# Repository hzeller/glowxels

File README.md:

Glowxels - Glow in the Dark Pixels
==================================

Driving 405nm LED line to make a pixelated glow-in-the-dark display.

This repo contains the addressed LED row, the rest is found in
https://github.com/hzeller/glowtape

The pitch is relatively small with 0.8mm for a width of 51.2mm with 64 LEDs.
It is achived with two rows of 1.6mm pitch with 0603 LED mounted in a
zig-zag pattern to have the adjacent pixels without visible gap in X-direction.

The row distance in Y-direction is 4 pixels apart (3.2mm), so even and odd
pixels in a row are sent 4 pixels spaced when sending.

The LEDs are driven by an [STP16CPC26]-chip - a neat 16 bit shift register with
constant current drivers. The serial data is just sent using the SPI bus
(with CS connected Latch), this is super-simple to wire.

The board carries 64 LEDs with two staggered rows of 0603 LEDs with a resulting
pixel-density of 0.8mm.

[STP16CPC26]: http://www.st.com/resource/en/datasheet/stp16cpc26.pdf

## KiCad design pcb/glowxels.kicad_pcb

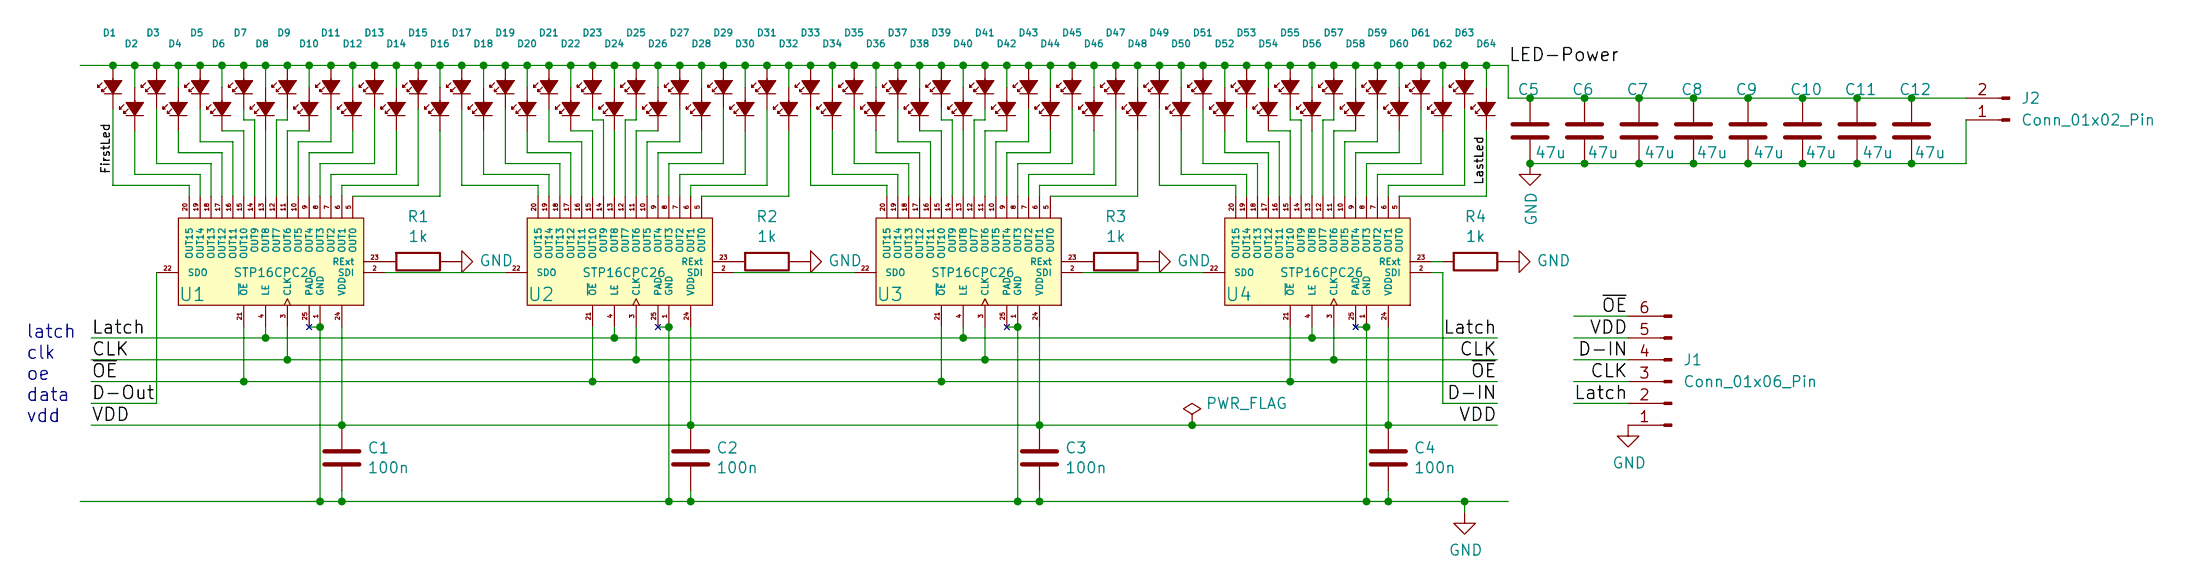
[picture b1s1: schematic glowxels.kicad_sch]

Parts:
C1, C2, C3, C4: 100n; C_0603_1608Metric
C5, C6, C7, C8, C9, C10, C11, C12: 47u; C_1210_3225Metric
D1, D2, D3, D4, D5, D6, D7, D8, D9, D10, D11, D12, D13, D14, D15, D16, D17, D18, D19, D20, D21, D22, D23, D24, D25, D26, D27, D28, D29, D30, D31, D32, D33, D34, D35, D36, D37, D38, D39, D40, D41, D42, D43, D44, D45, D46, D47, D48, D49, D50, D51, D52, D53, D54, D55, D56, D57, D58, D59, D60, D61, D62, D63, D64: UV; LED_0603_1608Metric
J1: Conn_01x06_Pin; PinHeader_1x06_P2.00mm_Vertical
J2: Conn_01x02_Pin; PinHeader_1x02_P2.00mm_Vertical
R1, R2, R3, R4: 1k; R_0603_1608Metric
U1, U2, U3, U4: STP16CPC26; TSSOP-24EP_4.4x7.8mm_Pitch0.65mm

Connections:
/CLK: J1.3, U1.3 (CLK), U2.3 (CLK), U3.3 (CLK), U4.3 (CLK)
/D-IN: J1.4, U4.2 (SDI)
/D-Out: U1.22 (SDO)
/FirstLed: D1.1 (K), U1.20 (OUT15)
/LED-Power: C5.1, C6.1, C7.1, C8.1, C9.1, C10.1, C11.1, C12.1, D1.2 (A), D2.2 (A), D3.2 (A), D4.2 (A), D5.2 (A), D6.2 (A), D7.2 (A), D8.2 (A), D9.2 (A), D10.2 (A), D11.2 (A), D12.2 (A), D13.2 (A), D14.2 (A), D15.2 (A), D16.2 (A), D17.2 (A), D18.2 (A), D19.2 (A), D20.2 (A), D21.2 (A), D22.2 (A), D23.2 (A), D24.2 (A), D25.2 (A), D26.2 (A), D27.2 (A), D28.2 (A), D29.2 (A), D30.2 (A), D31.2 (A), D32.2 (A), D33.2 (A), D34.2 (A), D35.2 (A), D36.2 (A), D37.2 (A), D38.2 (A), D39.2 (A), D40.2 (A), D41.2 (A), D42.2 (A), D43.2 (A), D44.2 (A), D45.2 (A), D46.2 (A), D47.2 (A), D48.2 (A), D49.2 (A), D50.2 (A), D51.2 (A), D52.2 (A), D53.2 (A), D54.2 (A), D55.2 (A), D56.2 (A), D57.2 (A), D58.2 (A), D59.2 (A), D60.2 (A), D61.2 (A), D62.2 (A), D63.2 (A), D64.2 (A), J2.2
/LastLed: D64.1 (K), U4.5 (OUT0)
/Latch: J1.2, U1.4 (LE), U2.4 (LE), U3.4 (LE), U4.4 (LE)
/VDD: C1.1, C2.1, C3.1, C4.1, J1.5, U1.24 (VDD), U2.24 (VDD), U3.24 (VDD), U4.24 (VDD)
/~OE: J1.6, U1.21 (~OE), U2.21 (~OE), U3.21 (~OE), U4.21 (~OE)
GND: C1.2, C2.2, C3.2, C4.2, C5.2, C6.2, C7.2, C8.2, C9.2, C10.2, C11.2, C12.2, J1.1, J2.1, R1.1, R2.1, R3.1, R4.1, U1.1 (GND), U1.25 (PAD), U2.1 (GND), U2.25 (PAD), U3.1 (GND), U3.25 (PAD), U4.1 (GND), U4.25 (PAD)
unnamed: D2.1 (K), U1.19 (OUT14)
unnamed: D3.1 (K), U1.18 (OUT13)
unnamed: D4.1 (K), U1.17 (OUT12)
unnamed: D5.1 (K), U1.16 (OUT11)
unnamed: D6.1 (K), U1.15 (OUT10)
unnamed: D7.1 (K), U1.14 (OUT9)
unnamed: D8.1 (K), U1.13 (OUT8)
unnamed: D9.1 (K), U1.12 (OUT7)
unnamed: D10.1 (K), U1.11 (OUT6)
unnamed: D11.1 (K), U1.10 (OUT5)
unnamed: D12.1 (K), U1.9 (OUT4)
unnamed: D13.1 (K), U1.8 (OUT3)
unnamed: D14.1 (K), U1.7 (OUT2)
unnamed: D15.1 (K), U1.6 (OUT1)
unnamed: D16.1 (K), U1.5 (OUT0)
unnamed: D17.1 (K), U2.20 (OUT15)
unnamed: D18.1 (K), U2.19 (OUT14)
unnamed: D19.1 (K), U2.18 (OUT13)
unnamed: D20.1 (K), U2.17 (OUT12)
unnamed: D21.1 (K), U2.16 (OUT11)
unnamed: D22.1 (K), U2.15 (OUT10)
unnamed: D23.1 (K), U2.14 (OUT9)
unnamed: D24.1 (K), U2.13 (OUT8)
unnamed: D25.1 (K), U2.12 (OUT7)
unnamed: D26.1 (K), U2.11 (OUT6)
unnamed: D27.1 (K), U2.10 (OUT5)
unnamed: D28.1 (K), U2.9 (OUT4)
unnamed: D29.1 (K), U2.8 (OUT3)
unnamed: D30.1 (K), U2.7 (OUT2)
unnamed: D31.1 (K), U2.6 (OUT1)
unnamed: D32.1 (K), U2.5 (OUT0)
unnamed: D33.1 (K), U3.20 (OUT15)
unnamed: D34.1 (K), U3.19 (OUT14)
unnamed: D35.1 (K), U3.18 (OUT13)
unnamed: D36.1 (K), U3.17 (OUT12)
unnamed: D37.1 (K), U3.16 (OUT11)
unnamed: D38.1 (K), U3.15 (OUT10)
unnamed: D39.1 (K), U3.14 (OUT9)
unnamed: D40.1 (K), U3.13 (OUT8)
unnamed: D41.1 (K), U3.12 (OUT7)
unnamed: D42.1 (K), U3.11 (OUT6)
unnamed: D43.1 (K), U3.10 (OUT5)
unnamed: D44.1 (K), U3.9 (OUT4)
unnamed: D45.1 (K), U3.8 (OUT3)
unnamed: D46.1 (K), U3.7 (OUT2)
unnamed: D47.1 (K), U3.6 (OUT1)
unnamed: D48.1 (K), U3.5 (OUT0)
unnamed: D49.1 (K), U4.20 (OUT15)
unnamed: D50.1 (K), U4.19 (OUT14)
unnamed: D51.1 (K), U4.18 (OUT13)
unnamed: D52.1 (K), U4.17 (OUT12)
unnamed: D53.1 (K), U4.16 (OUT11)
unnamed: D54.1 (K), U4.15 (OUT10)
unnamed: D55.1 (K), U4.14 (OUT9)
unnamed: D56.1 (K), U4.13 (OUT8)
unnamed: D57.1 (K), U4.12 (OUT7)
unnamed: D58.1 (K), U4.11 (OUT6)
unnamed: D59.1 (K), U4.10 (OUT5)
unnamed: D60.1 (K), U4.9 (OUT4)
unnamed: D61.1 (K), U4.8 (OUT3)
unnamed: D62.1 (K), U4.7 (OUT2)
unnamed: D63.1 (K), U4.6 (OUT1)
unnamed: R1.2, U1.23 (RExt)
unnamed: U1.2 (SDI), U2.22 (SDO)
unnamed: R2.2, U2.23 (RExt)
unnamed: U2.2 (SDI), U3.22 (SDO)
unnamed: R3.2, U3.23 (RExt)
unnamed: U3.2 (SDI), U4.22 (SDO)
unnamed: R4.2, U4.23 (RExt)

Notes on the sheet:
latch clk oe data vdd

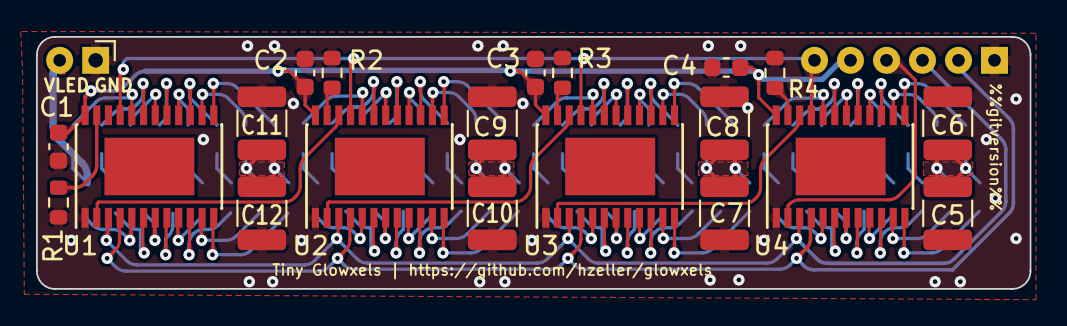
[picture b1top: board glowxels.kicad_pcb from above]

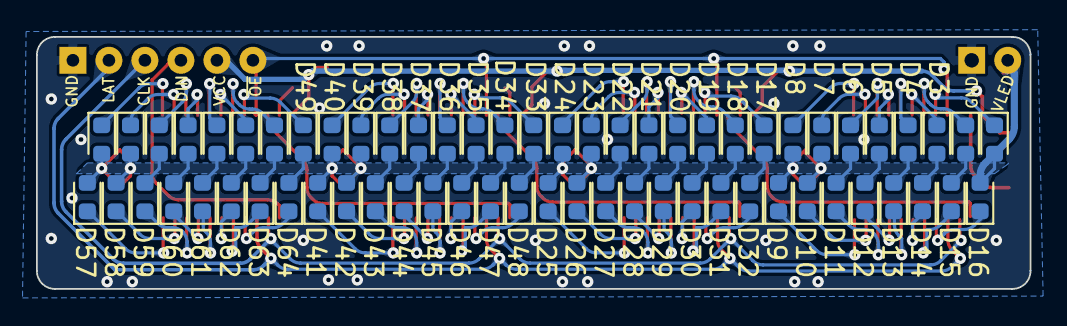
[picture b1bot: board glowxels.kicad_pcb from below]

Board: 2 copper layers, 55.2 x 14.0 mm, 86 parts (64 on the bottom side), 78 nets.

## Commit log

2017-12-22 Initial simple board.
    64 LEDs with a distance of 1.5mm (two offset rows 4.5mm apart,
    with 3mm distance between LEDs in each row).
2017-12-22 Use git version number in back silkscreen.
2017-12-22 Silkscreen optimization: mark power rails on back.
2018-01-30 Add OSHW silkscreen.
2018-01-30 Chaining connector: use space and increase pitch 1.27mm -> 2.0mm
2018-02-11 rename glowxels/ -> pcb/. Smallish tweak in PCB.
2018-02-11 Add submit.
2018-02-11 Fix markup.
2018-02-11 Add basic render.
2018-02-18 Move Glowxel emitting to separate class.
    o Create class GlowxelScreen where the screen control
    is encapcsulated.
    o since the current LED array is mounted backwards in
    the prototype, reverse all the bits.
2018-02-18 Only accelerate on first image. Simplify empty row code.
    o For multiple images, only the first image requires acceleration
    of the canvas. Make it so.
    o instead of a clunky nullptr comparison, just use the zeroed
    buffer for the empty data source for the y pixels that go
    beyond the range due to the zig-zag LED mounting.
2018-05-28 Fix sym-table to have a relative path. Also: update README.
2019-05-06 Smaller schematic render (forces less antialiasing in smaller display)
2019-05-06 Add inner edge fillet; connect LED power plane with thermal reliefs.
2022-01-01 Adapt to Kicad 6
2022-01-01 Use new versions ofr prl/pro files.
2024-09-02 Adapt to current kicad python lib.
2024-09-03 clean: use new name of directory.
2024-09-03 narrow: don't use old PCB
2024-09-29 Start board. Manually placed some LEDs.
    But hopefully this can be improved with a little script.
2024-09-30 Move LEDs according to their designator.
2024-09-30 Actually commit pcb. Also first traces for fir 16 LEDs
2024-10-01 First version, fully routed.
2024-10-01 Update with Labels.
2024-10-01 Update pictures for this branch.
2024-10-01 Some more GND layer stiching.
    The kind of fiddling with the design after it has been sent to
    fab already :)
2024-10-01 Add teardrops to through-holes and vias..
2024-10-01 Make fillet tracks.
2024-10-01 Add thermal relief gaps in ground plane.
    Setting must've disabled itself when setting another pour
    without gaps.
2024-10-25 Fix errornous Latch and CLK silkscreen swap.`
2024-10-30 Solder paste for TSSOP-EP: broken in smaller squares.
2024-11-01 Link to the other branch.
2024-11-01 Don't forget action image.
2024-11-01 Tease narrow version.
2024-11-01 Adapt README to the narrow version.
2024-11-02 Point to glowtape.
